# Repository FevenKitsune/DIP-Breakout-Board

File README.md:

# DIP-Breakout-Board

A simple breakout board to jury rig an IC into a project. Provides many new ways to misuse an IC. :)

Primarily made as a project to learn how to use KiCAD.

## Renders

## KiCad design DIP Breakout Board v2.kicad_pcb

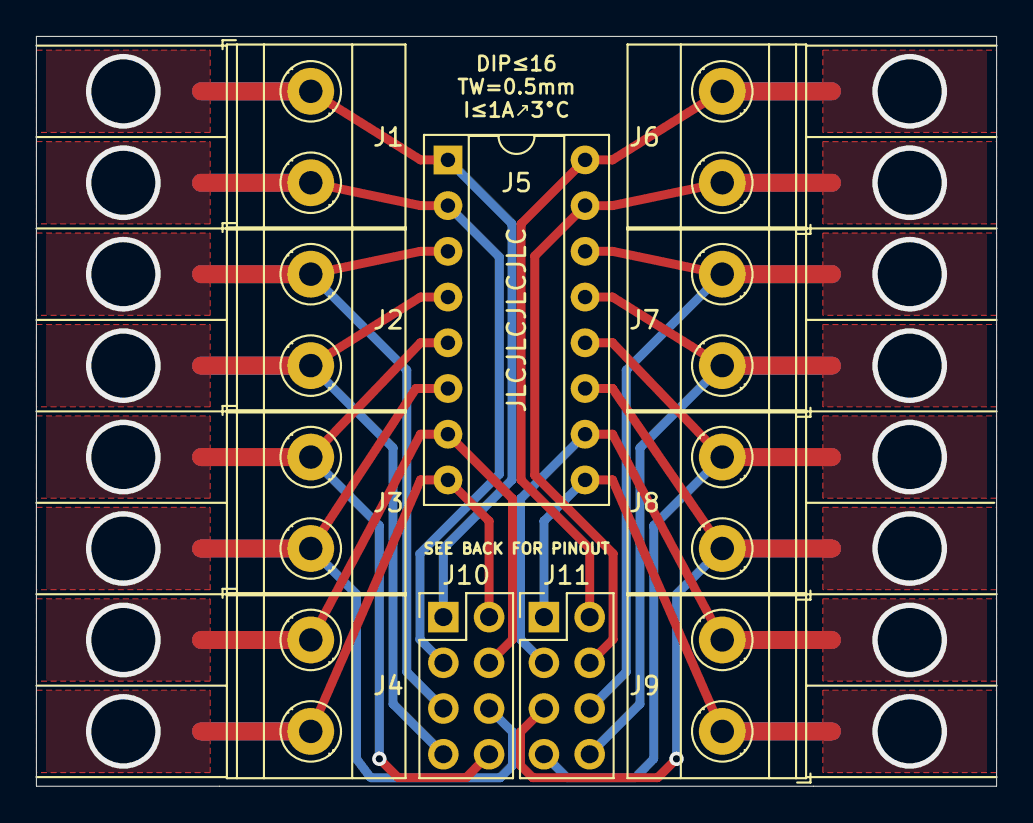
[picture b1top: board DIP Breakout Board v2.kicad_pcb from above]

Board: 2 copper layers, 53.3 x 41.7 mm, 11 parts (0 on the bottom side), 16 nets.

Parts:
J1, J2, J3, J4, J6, J7, J8, J9: Conn_01x02; TerminalBlock_Phoenix_MKDS-1,5-2-5.08_1x02_P5.08mm_Horizont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
J5: Conn_02x08_Counter_Clockwise; DIP-16_W7.62mm_Socket
J10: Conn_02x04_Counter_Clockwise; PinHeader_2x04_P2.54mm_Vertical
J11: Conn_02x04_Counter_Clockwise; PinHeader_2x04_P2.54mm_Vertical_Counter_Clockwise

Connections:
unnamed: J1.1, J5.1, J10.1
unnamed: J1.2, J5.2, J10.2
unnamed: J2.1, J5.3, J10.3
unnamed: J2.2, J5.4, J10.4
unnamed: J3.1, J5.5, J10.5
unnamed: J3.2, J5.6, J10.6
unnamed: J4.1, J5.7, J10.7
unnamed: J4.2, J5.8, J10.8
unnamed: J5.9, J9.1, J11.1
unnamed: J5.10, J9.2, J11.2
unnamed: J5.11, J8.1, J11.3
unnamed: J5.12, J8.2, J11.4
unnamed: J5.13, J7.1, J11.5
unnamed: J5.14, J7.2, J11.6
unnamed: J5.15, J6.1, J11.7
unnamed: J5.16, J6.2, J11.8

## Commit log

2021-01-28 Create a
2021-01-28 Update README.md
    Do I look like I know what a Markup is?
